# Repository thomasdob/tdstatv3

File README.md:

# TDstatv3
A USB-controlled potentiostat/galvanostat for thin-film battery characterization

## Introduction
This repository contains all the necessary design files to build your own USB-controlled potentiostat/galvanostat.
These files are intended as supplementary information accompanying the whitepaper at https://arxiv.org/pdf/1701.07650.pdf.

## Repository contents

### Directories
* `kicad`: KiCad design files (schematic diagram and PCB layout).
* `firmware`: Source code and compiled firmware for the PIC16F1459 microcontroller. Uses Microchip's XC8 compiler.
* `python`: Contains `tdstatv3.py`; run this file with Python 3 to bring up a GUI measurement tool.
* `gerber`: PCB design files in Gerber format, the universal standard for PCB manufacturing.
* `datasheets`: Datasheets in pdf format for the integrated circuits used in this design.
* `drivers`: Libusb drivers for Windows (not necessary on other operating systems).

### Files
* `full_schematic.pdf`: Complete schematic diagram in pdf format.
* `parts_list.txt`: Complete parts list, useful when ordering components.
* `pcb_3dview.png`: 3D renders of the PCB design, useful for verification of the PCB layout.
* `pcb_fabrication_diagram.pdf`: Front side of PCB with component locations and values, useful for circuit assembly.
* `photograph.jpg`: A photograph of the assembled circuit, using a PCB manufactured by [OSH Park](https://oshpark.com/).
* `LICENSE`: a copy of the GNU GPLv3 license.
* `README.md`: This file.

## USB access on Linux
In order to access the device without requiring root privileges, create a file
`/etc/udev/rules.d/99-tdstatv3.rules` containing the line

```
SUBSYSTEM=="usb", ATTRS{idVendor}=="a0a0", ATTRS{idProduct}=="0002", GROUP="plugdev", MODE="0666"
```
This assumes that the current user is a member of the `plugdev` group, and that the default USB Vendor and Product ID's
as coded in the microcontroller firmware are used; if not, these values need to be adjusted.

## Credits
* Thomas Dobbelaere
* email: thomas.dobbelaere@gmail.com

## License
The contents of this repository are licensed under the GNU General Public License (GPL).

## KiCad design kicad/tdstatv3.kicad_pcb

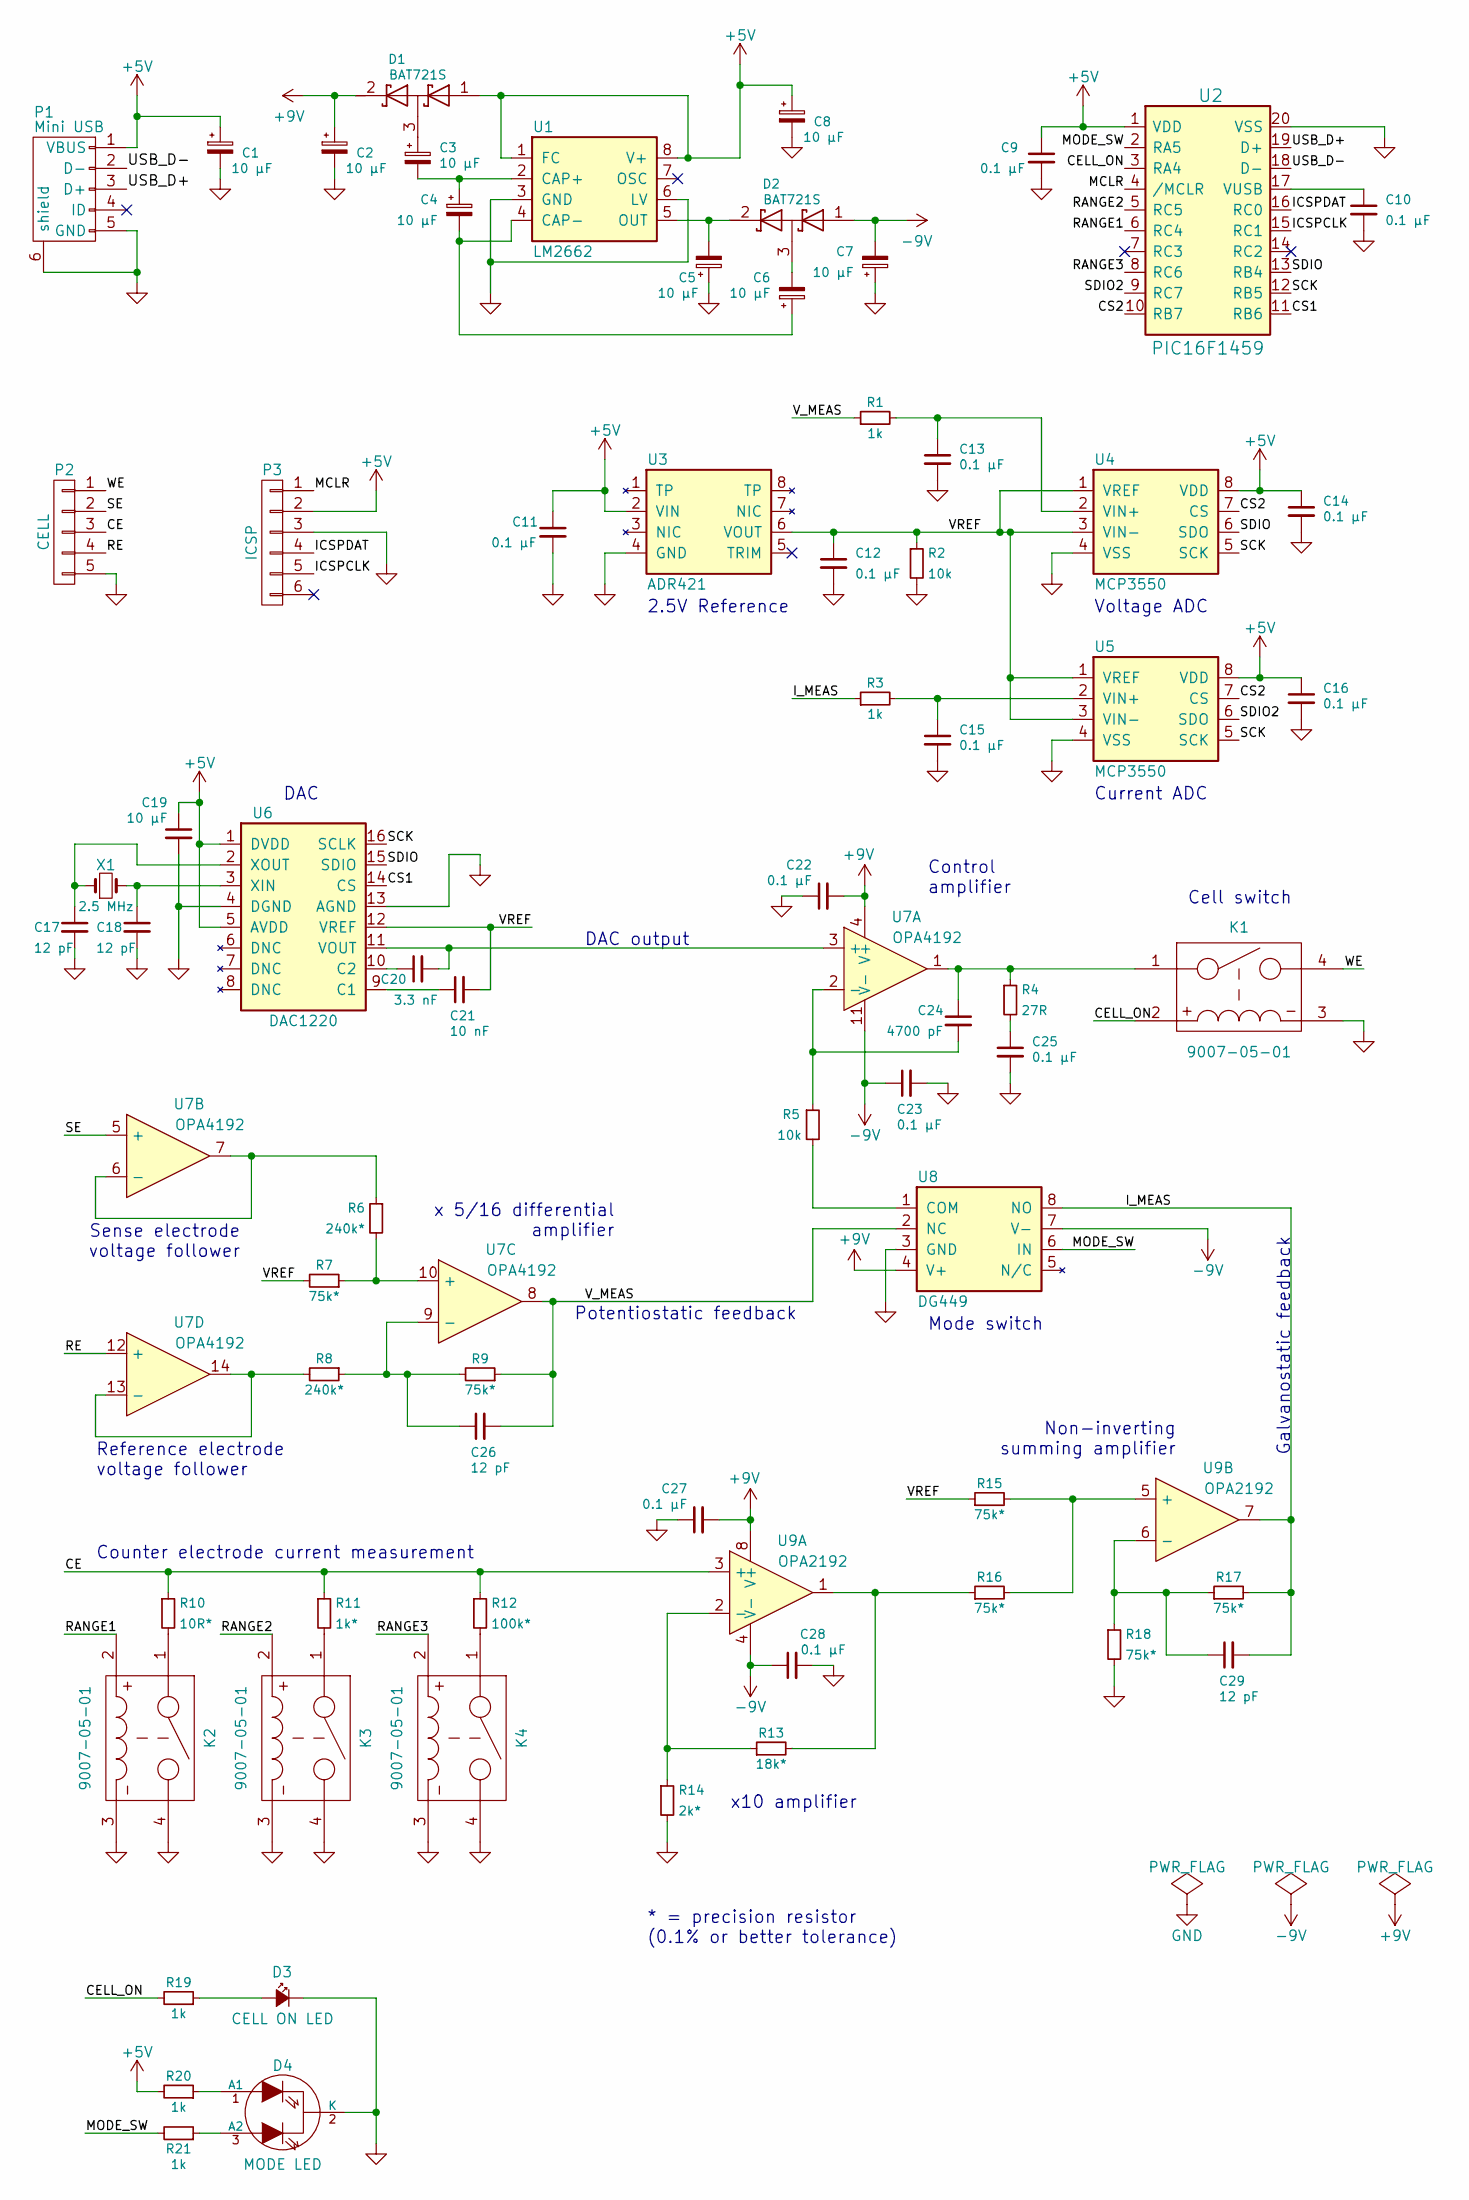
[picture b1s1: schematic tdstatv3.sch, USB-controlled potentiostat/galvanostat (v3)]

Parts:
C1, C2, C3, C4, C5, C6, C7, C8, C19: 10 µF; C_1210
C9, C10, C11, C12, C13, C14, C15, C16, C22, C23, C25, C27, C28: 0.1 µF; C_0805
C17, C18, C26, C29: 12 pF; C_0805
C20: 3.3 nF; C_0805
C21: 10 nF; C_0805
C24: 4700 pF; C_0805
D1, D2: BAT721S; SOT-23
D3: CELL ON LED; LED-3MM
D4: MODE LED; DUO-LED-3mm
K1, K2, K3, K4: 9007-05-01; RELAY-9007
P1: Mini USB; USB_Mini-B
P2: CELL; TerminalBlock_Phoenix_MKDS1_5_3mm5
P3: ICSP; Pin_Header_Straight_1x06
R1, R3, R19, R20, R21: 1k; R_0805
R2, R5: 10k; R_0805
R4: 27R; R_0805
R6, R8: 240k*; R_0805
R7, R9, R15, R16, R17, R18: 75k*; R_0805
R10: 10R*; R_0805
R11: 1k*; R_0805
R12: 100k*; R_0805
R13: 18k*; R_0805
R14: 2k*; R_0805
U1: LM2662; SOIC-8_3.9x4.9mm_Pitch1.27mm
U2: PIC16F1459; SOIC-20W_7.5x12.8mm_Pitch1.27mm
U3: ADR421; SOIC-8_3.9x4.9mm_Pitch1.27mm
U4, U5: MCP3550; SOIC-8_3.9x4.9mm_Pitch1.27mm
U6: DAC1220; SSOP-16_3.9x4.9mm_Pitch0.635mm
U7: OPA4192; SOIC-14_3.9x8.7mm_Pitch1.27mm
U8: DG449; sot23-8
U9: OPA2192; SOIC-8_3.9x4.9mm_Pitch1.27mm
X1: 2.5 MHz; Crystal_HC49-U_Vertical

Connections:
+5V: C1.1, C8.1, C9.1, C11.1, C14.1, C16.1, C19.1, D1.1 (A), P1.1 (VBUS), P3.2, R20.2, U1.1 (FC), U1.8 (V+), U2.1 (VDD), U3.2 (VIN), U4.8 (VDD), U5.8 (VDD), U6.1 (DVDD), U6.5 (AVDD)
+9V: C2.1, C22.2, C27.2, D1.2 (K), U7.4 (V+), U8.4 (V+), U9.8 (V+)
-9V: C7.2, C23.1, C28.1, D2.1 (A), U7.11 (V-), U8.7 (V-), U9.4 (V-)
/CE: P2.3, R10.1, R11.1, R12.1, U9.3 (+)
/CELL_ON: K1.2 (+), R19.2, U2.3 (RA4)
/CS1: U2.11 (RB6), U6.14 (CS)
/CS2: U2.10 (RB7), U4.7 (CS), U5.7 (CS)
/ICSPCLK: P3.5, U2.15 (RC1)
/ICSPDAT: P3.4, U2.16 (RC0)
/I_MEAS: C29.2, R3.1, R17.2, U8.8 (NO), U9.7
/MCLR: P3.1, U2.4 (/MCLR)
/MODE_SW: R21.2, U2.2 (RA5), U8.6 (IN)
/RANGE1: K2.2 (+), U2.6 (RC4)
/RANGE2: K3.2 (+), U2.5 (RC5)
/RANGE3: K4.2 (+), U2.8 (RC6)
/RE: P2.4, U7.12 (+)
/SCK: U2.12 (RB5), U4.5 (SCK), U5.5 (SCK), U6.16 (SCLK)
/SDIO: U2.13 (RB4), U4.6 (SDO), U6.15 (SDIO)
/SDIO2: U2.9 (RC7), U5.6 (SDO)
/SE: P2.2, U7.5 (+)
/USB_D+: P1.3 (D+), U2.19 (D+)
/USB_D-: P1.2 (D-), U2.18 (D-)
/VREF: C12.1, C21.2, R2.1, R7.2, R15.1, U3.6 (VOUT), U4.1 (VREF), U4.3 (VIN-), U5.1 (VREF), U5.3 (VIN-), U6.12 (VREF)
/V_MEAS: C26.2, R1.1, R9.1, U7.8, U8.2 (NC)
/WE: K1.4, P2.1
GND: C1.2, C2.2, C5.1, C7.1, C8.2, C9.2, C10.2, C11.2, C12.2, C13.2, C14.2, C15.2, C16.2, C17.2, C18.2, C19.2, C22.1, C23.2, C25.2, C27.1, C28.2, D3.1 (K), D4.2 (K), K1.3, K2.3, K2.4, K3.3, K3.4, K4.3, K4.4, P1.5 (GND), P1.6 (shield), P2.5, P3.3, R2.2, R14.2, R18.2, U1.3 (GND), U1.6 (LV), U2.20 (VSS), U3.4 (GND), U4.4 (VSS), U5.4 (VSS), U6.4 (DGND), U6.13 (AGND), U8.3 (GND)
unnamed: C3.1, D1.3 (common)
unnamed: C3.2, C4.1, U1.2 (CAP+)
unnamed: C4.2, C6.1, U1.4 (CAP-)
unnamed: C5.2, D2.2 (K), U1.5 (OUT)
unnamed: C6.2, D2.3 (common)
unnamed: C10.1, U2.17 (VUSB)
unnamed: C13.1, R1.2, U4.2 (VIN+)
unnamed: C15.1, R3.2, U5.2 (VIN+)
unnamed: C17.1, U6.2 (XOUT), X1.1
unnamed: C18.1, U6.3 (XIN), X1.2
unnamed: C20.1, U6.10 (C2)
unnamed: C20.2, U6.11 (VOUT), U7.3 (+)
unnamed: C21.1, U6.9 (C1)
unnamed: C24.1, K1.1, R4.1, U7.1
unnamed: C24.2, R5.1, U7.2 (-)
unnamed: C25.1, R4.2
unnamed: C26.1, R8.1, R9.2, U7.9 (-)
unnamed: C29.1, R17.1, R18.1, U9.6 (-)
unnamed: D3.2 (A), R19.1
unnamed: D4.1 (A1), R20.1
unnamed: D4.3 (A2), R21.1
unnamed: K2.1, R10.2
unnamed: K3.1, R11.2
unnamed: K4.1, R12.2
unnamed: R5.2, U8.1 (COM)
unnamed: R6.1, U7.6 (-), U7.7
unnamed: R6.2, R7.1, U7.10 (+)
unnamed: R8.2, U7.13 (-), U7.14
unnamed: R13.1, R14.1, U9.2 (-)
unnamed: R13.2, R16.1, U9.1
unnamed: R15.2, R16.2, U9.5 (+)

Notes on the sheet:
x 5/16 differential amplifier
Sense electrode voltage follower
Reference electrode voltage follower
Counter electrode current measurement
x10 amplifier
Non-inverting summing amplifier
Potentiostatic feedback
Galvanostatic feedback
Current ADC
Voltage ADC
2.5V Reference
Control amplifier
DAC
Mode switch
Cell switch
DAC output
* = precision resistor (0.1% or better tolerance)

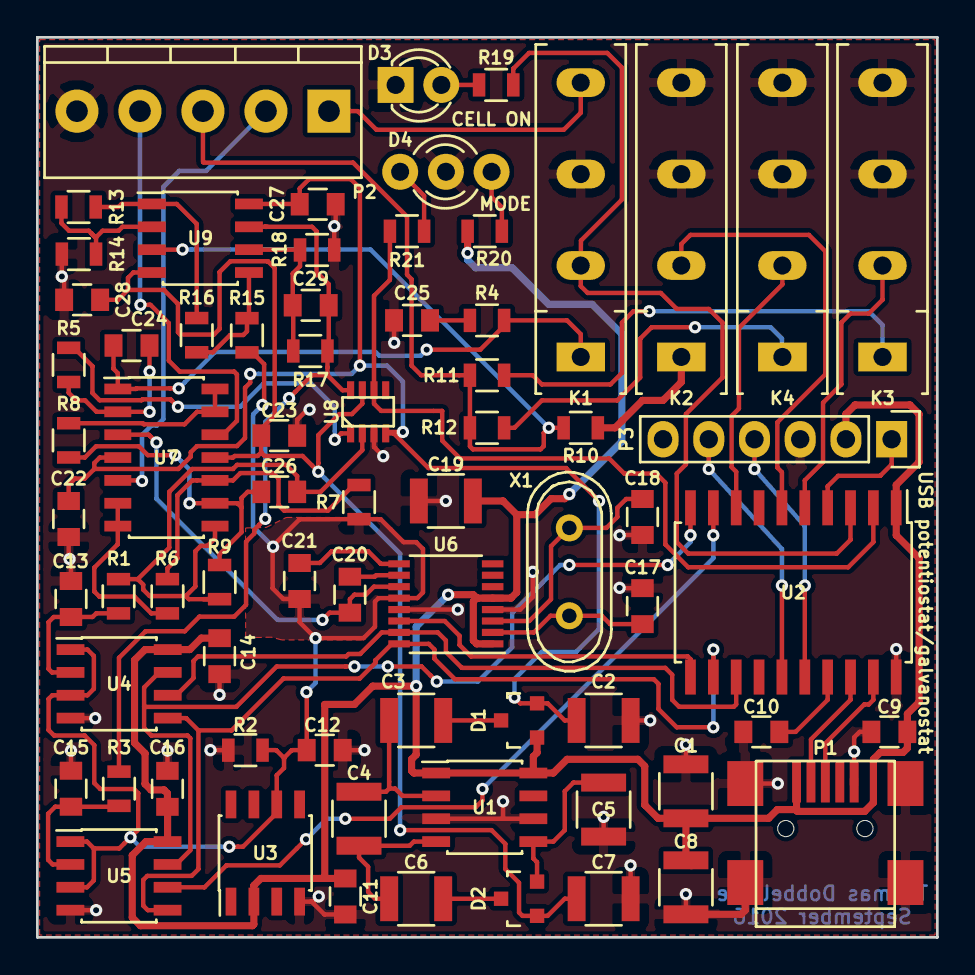
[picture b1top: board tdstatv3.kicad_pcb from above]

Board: 2 copper layers, 50.0 x 50.0 mm, 71 parts (0 on the bottom side), 57 nets.

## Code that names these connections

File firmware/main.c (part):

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#pragma config FOSC = INTOSC    // Oscillator Selection Bits (INTOSC oscillator: I/O function on CLKIN pin)
#pragma config WDTE = OFF       // Watchdog Timer Enable (WDT disabled)
#pragma config PWRTE = OFF      // Power-up Timer Enable (PWRT disabled)
#pragma config MCLRE = OFF      // MCLR Pin Function Select (MCLR/VPP pin function is digital input)
#pragma config CP = OFF         // Flash Program Memory Code Protection (Program memory code protection is disabled)
#pragma config BOREN = ON       // Brown-out Reset Enable (Brown-out Reset enabled)
#pragma config CLKOUTEN = OFF   // Clock Out Enable (CLKOUT function is disabled. I/O or oscillator function on the CLKOUT pin)
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
#define _XTAL_FREQ 48000000     // 48 MHz CPU clock frequency

#define MODE_SW_PIN LATAbits.LATA5
#define MODE_SW_TRIS TRISAbits.TRISA5
#define CELL_ON_PIN LATAbits.LATA4
#define CELL_ON_TRIS TRISAbits.TRISA4
#define CELL_ON  1
#define CELL_OFF 0
#define POTENTIOSTATIC  0
#define GALVANOSTATIC  1
#define INPUT  1
#define OUTPUT 0
#define RANGE1_PIN LATCbits.LATC4
#define RANGE1_TRIS TRISCbits.TRISC4
#define RANGE2_PIN LATCbits.LATC5
#define RANGE2_TRIS TRISCbits.TRISC5
#define RANGE3_PIN LATCbits.LATC6
#define RANGE3_TRIS TRISCbits.TRISC6

static const uint8_t* received_data;
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	ANSELC = 0x00; // digital I/O on PORTC
	APFCON = 0x00; // no funny alternate pins
	MODE_SW_TRIS = OUTPUT;
	MODE_SW_PIN = POTENTIOSTATIC; // initialize mode to potentiostatic
	CELL_ON_TRIS = OUTPUT;
	CELL_ON_PIN = CELL_OFF; // initialize cell to off position
	RANGE1_TRIS = OUTPUT;
	RANGE2_TRIS = OUTPUT;
	RANGE3_TRIS = OUTPUT;
	RANGE1_PIN = 1; // initialize range to range 1
	RANGE2_PIN = 0;
	RANGE3_PIN = 0;
	InitializeSPI();
	__delay_ms(25); // power-up delay - necessary for DAC1220
	DAC1220_Reset();
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
void command_cell_on()
{
	CELL_ON_PIN = CELL_ON;
	send_OK();
}

void command_cell_off()
{
	CELL_ON_PIN = CELL_OFF;
	send_OK();
}

void command_mode_potentiostatic()
{
	MODE_SW_PIN = POTENTIOSTATIC;
	send_OK();
}

void command_mode_galvanostatic()
{
	MODE_SW_PIN = GALVANOSTATIC;
	send_OK();
}

void command_range1()
{
    RANGE1_PIN = 1;
    __delay_ms(10); // make the new relay setting before breaking the old one
    RANGE2_PIN = 0;
    RANGE3_PIN = 0;
	send_OK();
}

void command_range2()
{
    RANGE2_PIN = 1;
    __delay_ms(10); // make the new relay setting before breaking the old one
    RANGE1_PIN = 0;
    RANGE3_PIN = 0;
	send_OK();
}

void command_range3()
{
    RANGE3_PIN = 1;
    __delay_ms(10); // make the new relay setting before breaking the old one
    RANGE1_PIN = 0;
    RANGE2_PIN = 0;
	send_OK();
}

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
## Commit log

2017-06-16 Create LICENSE
2017-06-16 Added license information
2017-08-22 Added suggested Digikey part numbers
2017-08-22 Converted code to python3; added comments; added logging functionality
2017-11-06 Update contact information
2022-05-10 remove DeprecationWarning: Accessing pyqtgraph.QtWidgets through QtGui is deprecated and will be removed sometime after May 2022. Use QtWidgets.QPlainTextEdit instead.
2022-05-10 more deprecation warnings
